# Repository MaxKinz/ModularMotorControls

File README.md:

"# ModularMotorControls" 
This is going to be a motor control project loosely based on the famous "VESC" project by benjamin vedder. 
So why another open source motor controller ? Well-mainly for modularity
The ultimate goal is to have a controller that does exactly what you need for a good price on every level wether you need to move some small 4000kv hobby rc motor or a full industrial Servo at 400V. Obviously the hardware required for the servo would be overkill and too expensive for the small motor while having additional limitations. 
Therefore hardware is going to be split into 3 categories that first have to be defined with all their requirements resulting in interfaces. A design requirement is that every implementation of one of those categories is compatible with every implementation of the two others so if for instance 3 implementations of each exist one could configure 27 different controllers. There will however be compatibility ranges between category 2 and 3 as it is impossible to completely seperate them. 

Here are the the categories :
  1. A logic board containing at least an STM32 microprocessor 
    -Variants with more or less calc power (closed loop control vs. open loop, BLDC or FOC..... Position/speed etc control) 
    -interfaces (CAN,I²C,UART,SPI....)
    -peripherals (IMUs,Bluetooth,ZigBee,LoRa or whatever comes to mind)    
    -may also be implemented breakout boards for readily available ebay bords
  
  2. A predriver stage containing MOSFET drivers as well as all the voltage "grooming" buck and boost converters (mainly different   
     different target Voltages)
     - "all in one"- solutions like the TI DRV8302
     - or discrete mosfet drivers and buck converters shunt amps 
     
  3. A power stage containing the main leads, the big input filter caps, and of course the MOSFETs/IGBTs, shunts,temp sense (mainly 
     different target currents but also voltages) 
     - all MOSFETs on one side or using both sides - different temp sensors,
     - SMD, THT , radiators,etc...
  
So as you can see I mainly just split up the usual components of a motor driver - big whoop - so what is this about ? 
Well - I would love to have defined interfaces between those parts. It would make it easy to reuse software that is otherwise rewritten over and over. It would also make it loads cheaper if by overloading your robot you yet again blew up a driver - and now conveniently only replace the power board (or if you are not so lucky power and predriver) 
All of my work on this will be open source. Since I plan on repurposing some of the VESC software which is based on ChibiOS and ChibiOS is GPL I might be forced to use GPL for the first iteration. However I am not a big fan of the agressive approach the GPL takes on open source which, if you are honest, resticts projects to hobby use as no employer I know wants his/her IP he payed you to create out there....so I would love to write some code under, for example, Apache liscense later in the process so truely anyone can use the controller even if you use it for work.

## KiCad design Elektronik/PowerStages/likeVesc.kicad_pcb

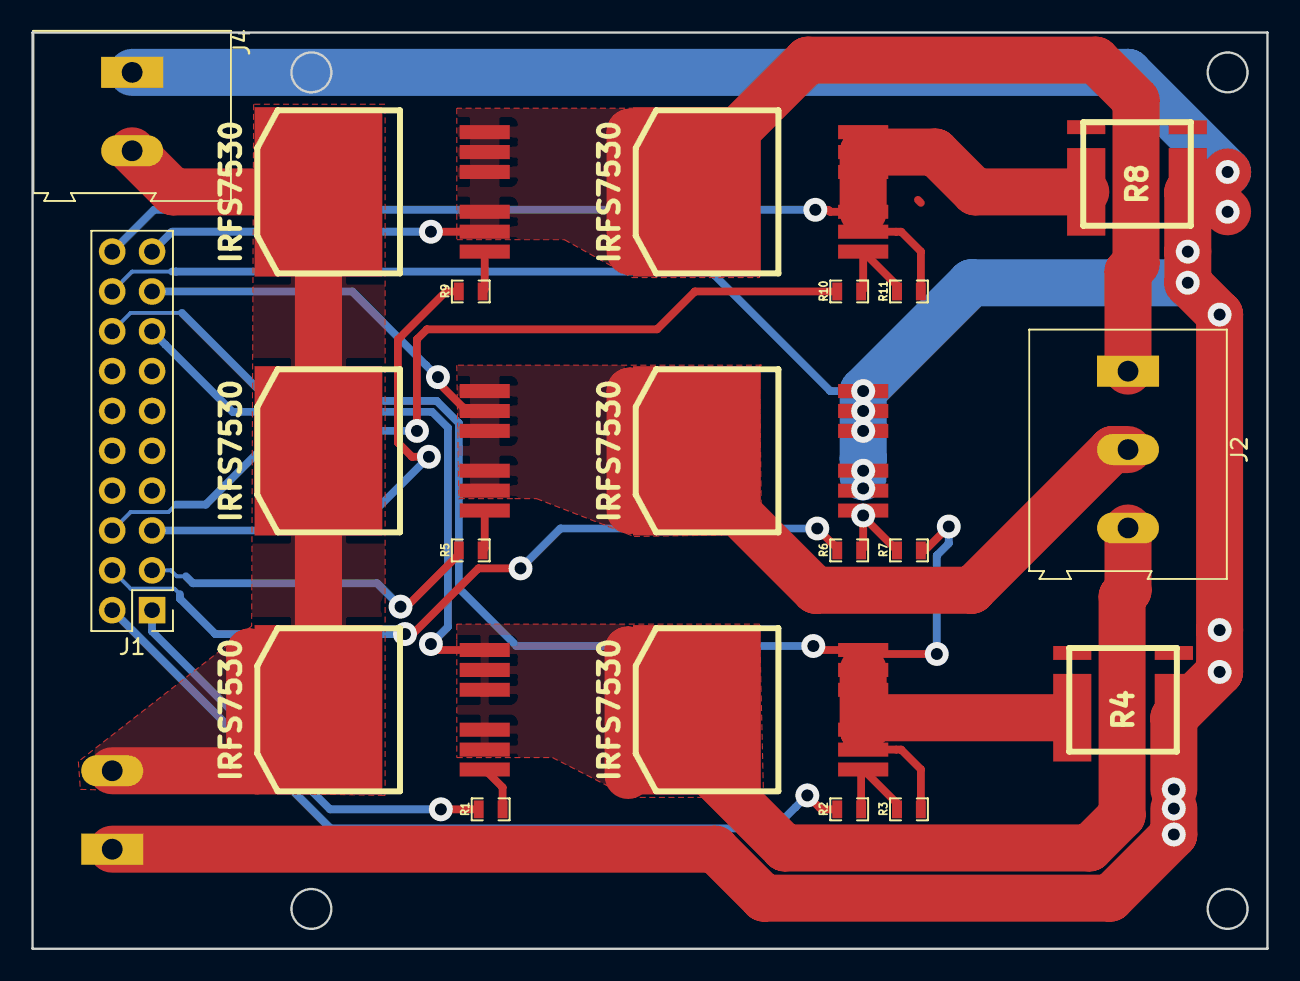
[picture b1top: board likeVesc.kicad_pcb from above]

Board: 2 copper layers, 78.7 x 58.4 mm, 21 parts (1 on the bottom side), 19 nets.

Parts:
J1: CONN_02X10; Pin_Header_Straight_2x10_Pitch2.54mm
J2: Screw_Terminal_1x03; TerminalBlock_Altech_AK300-3_P5.00mm
J3, J4: Screw_Terminal_1x02; TerminalBlock_Altech_AK300-2_P5.00mm
Q1, Q2, Q3, Q4, Q5, Q6: IRFS7530; D2PAK-7-GDS
R1, R2, R5, R6, R9, R10: 4R7; SMD-0603_r
R3, R7, R11: 39k; SMD-0603_r
R4, R8: SHUNT; WSLP2726

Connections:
/BenMosfets/H1_LOW: J1.16, Q2.S, R3.1, R4.1, R7.1
/BenMosfets/H1_VS: J1.15, J2.3, Q1.S, Q2.D
/BenMosfets/H2_VS: J1.17, J2.2, Q3.S, Q4.D
/BenMosfets/H3_LOW: J1.20, Q6.S, R8.1, R11.1
/BenMosfets/H3_VS: J1.19, J2.1, Q5.S, Q6.D
/BenMosfets/M_H1: J1.1, R1.2
/BenMosfets/M_H2: J1.3, R5.2
/BenMosfets/M_H3: J1.5, R9.2
/BenMosfets/M_L1: J1.2, R2.2
/BenMosfets/M_L2: J1.4, R6.2
/BenMosfets/M_L3: J1.6, R10.2
GND: J1.18, J3.1, J4.1, Q4.S, R4.2, R8.2
unnamed: Q1.G, R1.1
unnamed: Q2.G, R2.1, R3.2
unnamed: Q3.G, R5.1
unnamed: Q4.G, R6.1, R7.2
unnamed: Q5.G, R9.1
unnamed: Q6.G, R10.1, R11.2
V_SUPPLY: J3.2, J4.2, Q1.D, Q3.D, Q5.D

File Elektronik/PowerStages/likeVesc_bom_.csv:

Component,Description,Part,References,Value,Footprint,Quantity Per PCB,Datasheet
1,"Connector, double row, 02x10, pin header",CONN_02X10,J1,CONN_02X10,Pin_Header_Straight_2x10_Pitch2.54mm,1,
2,2-pin screw terminal connector,Screw_Terminal_1x02,J3 J4,Screw_Terminal_1x02,TerminalBlock_Altech_AK300-2_P5.00mm,2,
3,3-pin screw terminal connector,Screw_Terminal_1x03,J2,Screw_Terminal_1x03,TerminalBlock_Altech_AK300-3_P5.00mm,1,
4,,MOSFET_N,Q1 Q2 Q3 Q4 Q5 Q6,IRFS7530,D2PAK-7-GDS,6,
5,,R-RESCUE-BLDC_4,R3 R7 R11,39k,SMD-0603_r,3,
6,,R-RESCUE-BLDC_4,R1 R2 R5 R6 R9 R10,4R7,SMD-0603_r,6,
7,,SHUNT,R4 R8,SHUNT,WSLP2726,2,





Component Groups:,7
Component Count:,21
Fitted Components:,21
Number of PCBs:,1
Total components:,21
Schematic Version:,
Schematic Date:,
BoM Date:,22.05.2018 20:13:28
Schematic Source:,F:/git/ModularMotorControl/Elektronik/PowerStages/likeVesc.sch
KiCad Version:,Eeschema 4.0.6

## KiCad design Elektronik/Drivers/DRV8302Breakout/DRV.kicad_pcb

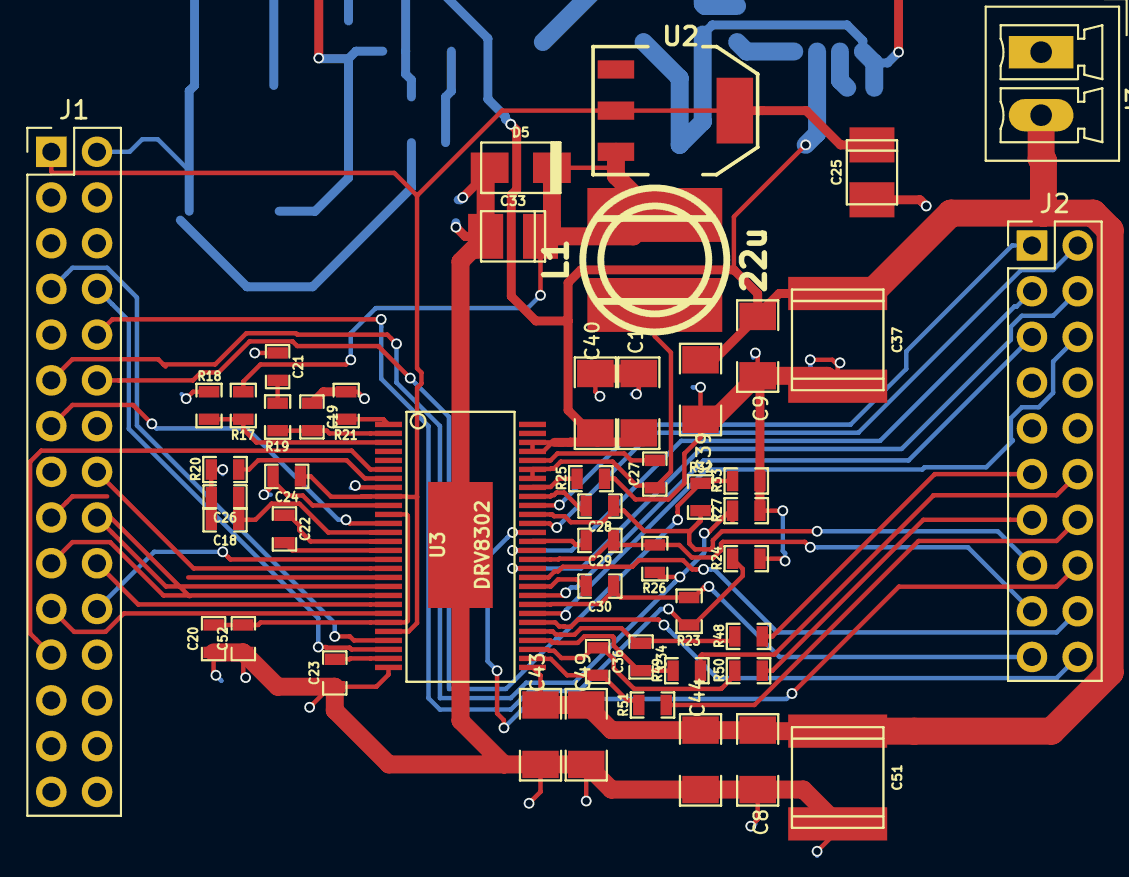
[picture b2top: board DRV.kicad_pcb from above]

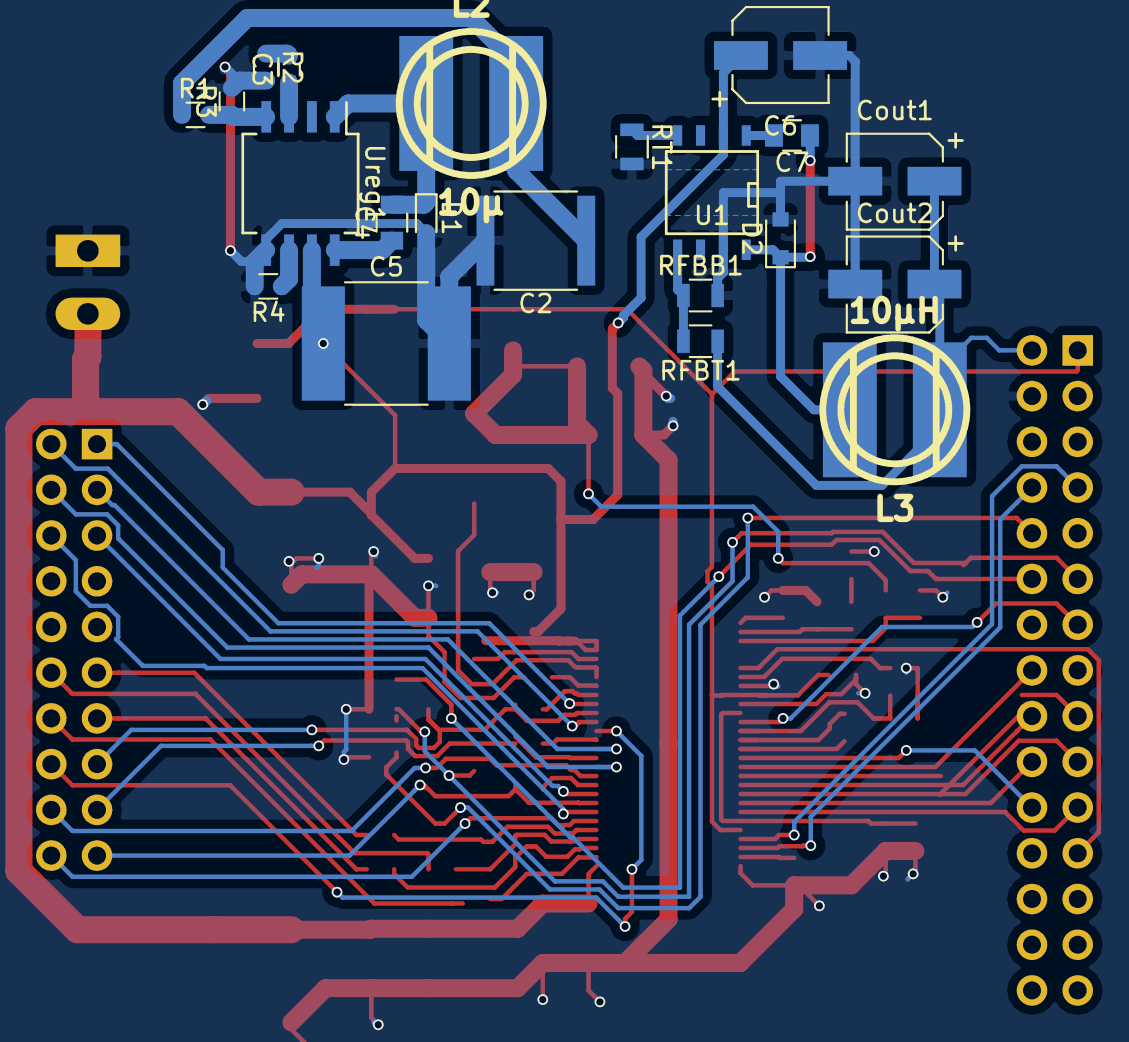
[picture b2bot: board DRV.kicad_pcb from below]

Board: 2 copper layers, 71 parts (21 on the bottom side), 66 nets.

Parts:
C1, C8, C9, C39, C40, C43, C44, C49: 10u,50V; SMD-1206
C2: 22μ; C_2220
C3: 470pF; C_0603
C4: 100nF; C_0805
C5: 10μF; C_2225_HandSoldering
C6: 10μF; CP_Elec_5x5.3
C7: 0.1μF; C_0805
C18, C20, C23, C24, C26, C52: 2.2u; SMD-0603_c
C19: 120p; SMD-0603_c
C21: 6.8n; SMD-0603_c
C22: 22n; SMD-0603_c
C25, C33: 100u; c_tant_B
C27: 100n; SMD-0603_c
C28, C29, C30: 220n; SMD-0603_c
C34, C36: 2.2n; SMD-0603_c
C37: 15u,100V; c_2220
C51: 15u, 100v; c_2220
Cout1, Cout2: 33μF; CP_Elec_5x5.3
D1: D_Schottky; D_0603
D2: D_Schottky_75V; D_0805
D5: TVS 5V; do214ac
J1: CONN_CPU; Pin_Header_Straight_2x15_Pitch2.54mm
J2: Conn_POWER; Pin_Header_Straight_2x10_Pitch2.54mm
J3: Screw_Terminal_1x02; PhoenixContact_MCV-G_02x3.50mm_Vertical
L1: 22u; inductor_smd_8x5mm
L2: 10μ; inductor_smd_8x5mm
L3: 10μH; inductor_smd_8x5mm
R1: 127k; R_0603
R2: 16k; R_0603
R3: 40.2k; R_0603
R4: 200k; R_0603
R17: 18k; SMD-0603_r
R18: 3k3; SMD-0603_r
R19: 15k; SMD-0603_r
R20: 10k; SMD-0603_r
R21: 220k; SMD-0603_r
R23, R26, R32: 39k; SMD-0603_r
R24, R27, R33: 2k2; SMD-0603_r
R25: 1M; SMD-0603_r
R48, R49, R50, R51: 100R; SMD-0603_r
RFBB1: 17.8k; R_0805
RFBT1: 100k; R_0805
RT1: 41,2k; R_0805
U1: LMR16020; SOIC-8-N
U2: TC2117; SOT-223
U3: DRV8302; TSSOP-56-PP
Ureg1: MP4559; SO-8_5.3x6.2mm_Pitch1.27mm

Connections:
+5V: C33.1, D5.2, L1.2, R17.1, U2.3
+12V: C2.1, L2.2, R1.1
/5vReg/5V: Cout1.1, Cout2.1, J1.2, L3.1, RFBT1.1
/DRV/BR_SO1: J1.7, U3.25
/DRV/BR_SO2: J1.8, U3.26
/DRV/DC_CAL: J1.13, U3.12
/DRV/EN_GATE: J1.22, U3.16
/DRV/FAULT: J1.23, U3.6
/DRV/H1: J1.16, U3.17
/DRV/H1_LOW: J2.16, U3.44
/DRV/H1_VS: C28.1, J2.15, R32.1, U3.46
/DRV/H2: J1.18, U3.19
/DRV/H2_LOW: J2.18, U3.39
/DRV/H2_VS: C29.1, J2.17, R26.1, U3.41
/DRV/H3: J1.20, U3.21
/DRV/H3_LOW: J2.20, U3.34
/DRV/H3_VS: C30.1, J2.19, R23.1, U3.36
/DRV/L1: J1.17, U3.18
/DRV/L2: J1.19, U3.20
/DRV/L3: J1.21, U3.22
/DRV/M_H1: J2.1, U3.47
/DRV/M_H2: J2.3, U3.42
/DRV/M_H3: J2.5, U3.37
/DRV/M_L1: J2.2, U3.45
/DRV/M_L2: J2.4, U3.40
/DRV/M_L3: J2.6, U3.35
/DRV/SENS1: J1.10, R23.2, R24.2
/DRV/SENS2: J1.11, R26.2, R27.2
/DRV/SENS3: J1.12, R32.2, R33.2
/DRV/SH1_A: J2.11, R48.1
/DRV/SH1_B: J2.12, R49.1
/DRV/SH2_A: J2.13, R50.1
/DRV/SH2_B: J2.14, R51.1
GND: C1.1, C2.2, C5.2, C6.2, C8.1, C9.1, C18.2, C19.1, C20.1, C21.1, C23.1, C24.2, C25.2, C26.2, C33.2, C37.1, C39.1, C40.1, C43.2, C44.2, C49.2, C51.1, C52.1, Cout1.2, Cout2.2, D1.2, D2.2, D5.1, J1.4, J3.1, R2.2, R3.2, R4.2, R18.2, R20.2, R21.1, R24.1, R25.1, R27.1, R33.1, RFBB1.2, RT1.2, U1.7, U3.8, U3.10, U3.28, U3.57, Ureg1.5
unnamed: C3.1, Ureg1.3
unnamed: C3.2, R2.1
unnamed: C4.1, Ureg1.8
unnamed: C4.2, D1.1, L2.1, Ureg1.1
unnamed: C7.1, D2.1, L3.2, U1.8
unnamed: C7.2, U1.1
unnamed: C18.1, C26.1, U3.13
unnamed: C19.2, R19.2, U3.2
unnamed: C20.2, C52.2, U3.11, U3.23
unnamed: C21.2, R19.1
unnamed: C22.1, U3.14
unnamed: C22.2, U3.15
unnamed: C23.2, U3.27
unnamed: C27.1, L1.1, U3.50, U3.51
unnamed: C27.2, U3.52
unnamed: C28.2, U3.48
unnamed: C29.2, U3.43
unnamed: C30.2, U3.38
unnamed: C34.1, R48.2, U3.33
unnamed: C34.2, R49.2, U3.32
unnamed: C36.1, R50.2, U3.31
unnamed: C36.2, R51.2, U3.30
unnamed: R1.2, R3.1, Ureg1.4
unnamed: R4.1, Ureg1.6
unnamed: R17.2, R18.1, U3.3
unnamed: R20.1, U3.7
unnamed: R21.2, U3.1
unnamed: R25.2, U3.49
unnamed: RFBB1.1, RFBT1.2, U1.5
unnamed: RT1.1, U1.4
VCC: C24.1, C25.1, J1.1, U2.2, U3.9, U3.24
V_SUPPLY: C1.2, C5.1, C6.1, C8.2, C9.2, C37.2, C39.2, C40.2, C43.1, C44.1, C49.1, C51.2, J3.2, U1.2, U3.29, U3.53, U3.54, Ureg1.7

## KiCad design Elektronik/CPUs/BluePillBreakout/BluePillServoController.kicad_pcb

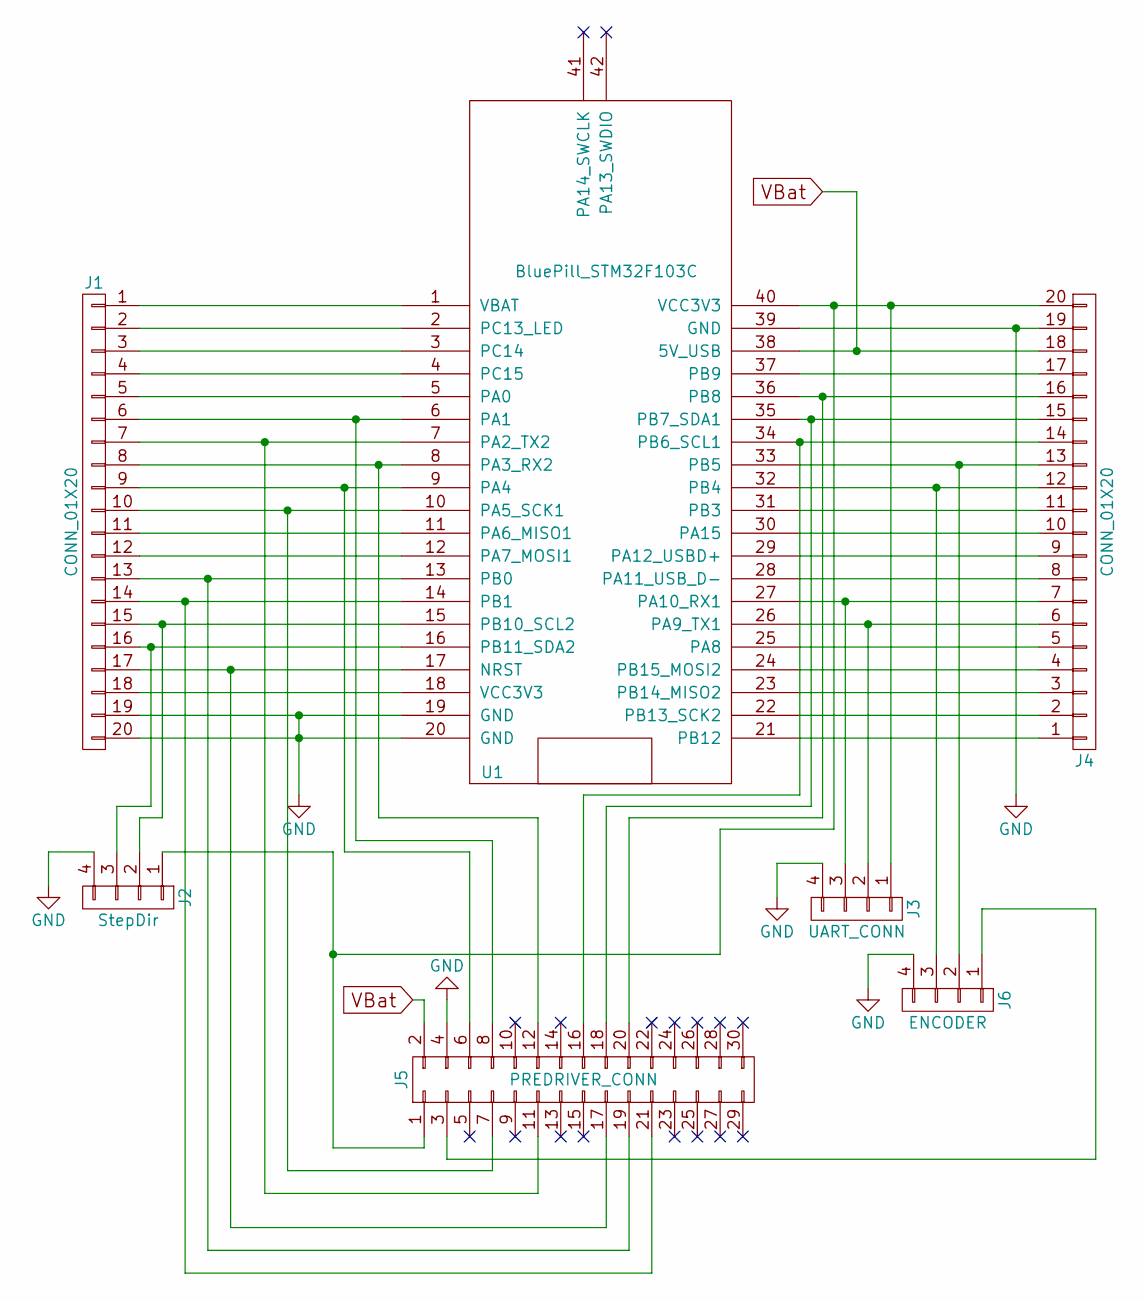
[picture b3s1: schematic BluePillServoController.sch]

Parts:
J1, J4: CONN_01X20; Pin_Header_Straight_1x20_Pitch2.54mm
J2: StepDir; Pin_Header_Straight_1x04_Pitch2.54mm
J3: UART_CONN; Pin_Header_Straight_1x04_Pitch2.54mm
J5: PREDRIVER_CONN; Pin_Header_Straight_2x15_Pitch2.54mm
J6: ENCODER; Pin_Header_Straight_1x04_Pitch2.54mm
U1: BluePill_STM32F103C

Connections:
GND: J1.19, J1.20, J2.4, J3.4, J4.19, J5.4, J6.4, U1.19 (GND), U1.20 (GND), U1.39 (GND)
unnamed: J1.1, U1.1 (VBAT)
unnamed: J1.2, U1.2 (PC13_LED)
unnamed: J1.3, U1.3 (PC14)
unnamed: J1.4, U1.4 (PC15)
unnamed: J1.5, U1.5 (PA0)
unnamed: J1.6, J5.8, U1.6 (PA1)
unnamed: J1.7, J5.11, U1.7 (PA2_TX2)
unnamed: J1.8, J5.12, U1.8 (PA3_RX2)
unnamed: J1.9, J5.6, U1.9 (PA4)
unnamed: J1.10, J5.7, U1.10 (PA5_SCK1)
unnamed: J1.11, U1.11 (PA6_MISO1)
unnamed: J1.12, U1.12 (PA7_MOSI1)
unnamed: J1.13, J5.19, U1.13 (PB0)
unnamed: J1.14, J5.21, U1.14 (PB1)
unnamed: J1.15, J2.2, U1.15 (PB10_SCL2)
unnamed: J1.16, J2.3, U1.16 (PB11_SDA2)
unnamed: J1.17, J5.17, U1.17 (NRST)
unnamed: J1.18, U1.18 (VCC3V3)
unnamed: J2.1, J3.1, J4.20, J5.1, U1.40 (VCC3V3)
unnamed: J3.2, J4.6, U1.26 (PA9_TX1)
unnamed: J3.3, J4.7, U1.27 (PA10_RX1)
unnamed: J4.1, U1.21 (PB12)
unnamed: J4.2, U1.22 (PB13_SCK2)
unnamed: J4.3, U1.23 (PB14_MISO2)
unnamed: J4.4, U1.24 (PB15_MOSI2)
unnamed: J4.5, U1.25 (PA8)
unnamed: J4.8, U1.28 (PA11_USB_D-)
unnamed: J4.9, U1.29 (PA12_USBD+)
unnamed: J4.10, U1.30 (PA15)
unnamed: J4.11, U1.31 (PB3)
unnamed: J4.12, J6.3, U1.32 (PB4)
unnamed: J4.13, J6.2, U1.33 (PB5)
unnamed: J4.14, J5.16, U1.34 (PB6_SCL1)
unnamed: J4.15, J5.18, U1.35 (PB7_SDA1)
unnamed: J4.16, J5.20, U1.36 (PB8)
unnamed: J4.17, U1.37 (PB9)
unnamed: J5.3, J6.1
VBat: J4.18, J5.2, U1.38 (5V_USB)

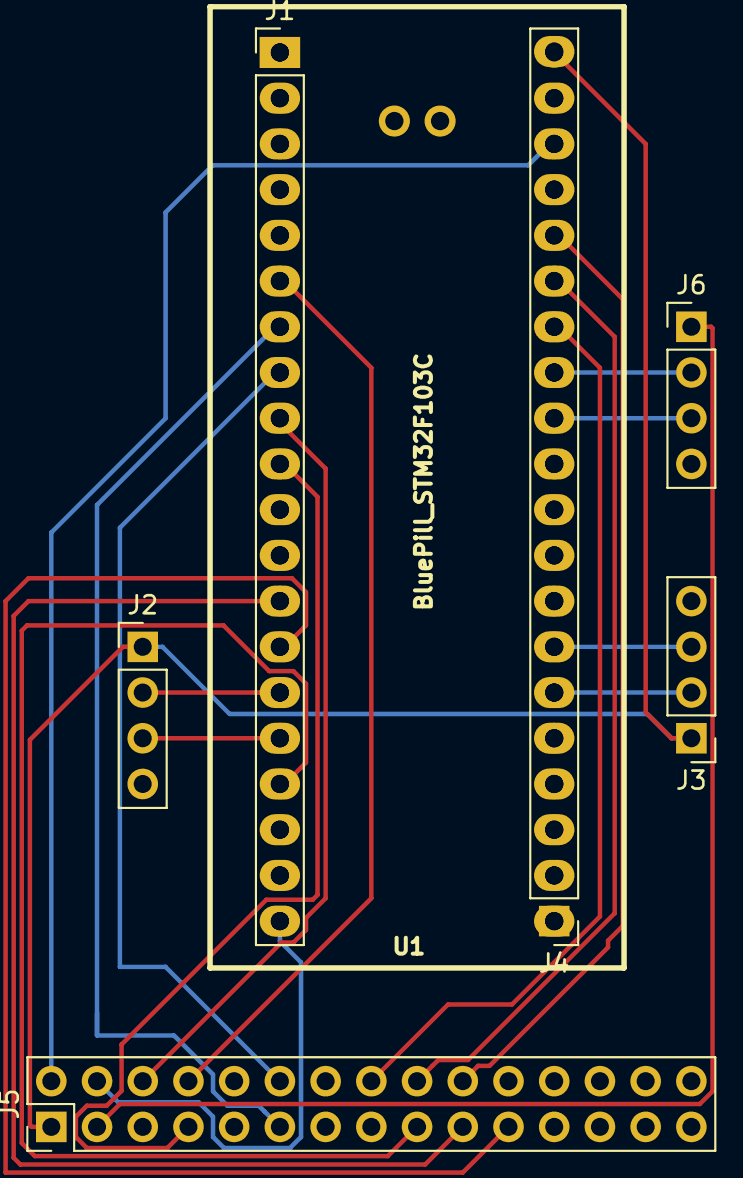
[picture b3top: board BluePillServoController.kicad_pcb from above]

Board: 2 copper layers, 7 parts (0 on the bottom side), 39 nets.

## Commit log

2018-05-16 Defined some connections (See Requirements.ods) First Breakout for BluePill Routed
2018-05-16 DriverProjectAddedJustBeginningFromVESCSchematic
2018-05-17 FirstPowerSchematic
2018-05-17 FirstDriverBegun
2018-05-17 fewChanges
2018-05-19 Added some buck converter schematics
2018-05-20 first driver pcb most things routed missnig power connector
2018-05-20 recommit as last didnt work
2018-05-20 added power connection to driver board
2018-05-22 added a power stage
2018-05-29 firstStm42f4
